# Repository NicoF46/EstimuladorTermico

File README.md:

# EstimuladorTermico
Estimulador térmico para trabajo profesional

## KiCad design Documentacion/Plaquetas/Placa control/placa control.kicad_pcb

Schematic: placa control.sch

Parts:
A1: Arduino_Nano_v3.x; Arduino_Nano
C1: 2u; C_Disc_D4.7mm_W2.5mm_P5.00mm
C2, C9: 100n; C_Disc_D4.7mm_W2.5mm_P5.00mm
C3: 330n; C_Disc_D4.7mm_W2.5mm_P5.00mm
C4, C6: 2.2n; C_Disc_D4.7mm_W2.5mm_P5.00mm
C7: 4700u; C_Radial_D16.0mm_H25.0mm_P7.50mm
C8: 4.7u; C_Rect_L29.0mm_W9.1mm_P27.50mm_MKT
C10, C11: 4.7n; C_Disc_D4.7mm_W2.5mm_P5.00mm
D1: 1N4002; D_DO-41_SOD81_P10.16mm_Horizontal
D6: Yellow; D_A-405_P7.62mm_Horizontal
D7: Green; D_A-405_P7.62mm_Horizontal
D8: RED; D_A-405_P7.62mm_Horizontal
J1, J5, J8: Conn_01x02_Male; PinHeader_1x02_P2.54mm_Vertical
J2: DB9_Female_MountingHoles; DSUB-9_Female_Horizontal_P2.77x2.84mm_EdgePinOffset7.70mm_H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
J3: Screw_Terminal_01x02; TerminalBlock_bornier-2_P5.08mm
J4: Conn_01x06_Male; PinHeader_1x06_P2.54mm_Vertical
J6: Conn_01x04_Male; PinHeader_1x04_P2.54mm_Vertical
J7: Conn_02x05_Counter_Clockwise; PinHeader_2x05_P2.54mm_VerticalNico
J9: Conn_01x08_Male; PinHeader_1x08_P2.54mm_Vertical
J10: Conn_01x06_Female; PinHeader_1x06_P2.54mm_Vertical
J11, J12, J13: Conn_01x03_Male; PinHeader_1x03_P2.54mm_Vertical
Q1, Q2, Q7, Q8, Q9: BC548; TO-92_HandSolder
R1, R2, R18, R19, R20: 220; R_Axial_DIN0414_L11.9mm_D4.5mm_P15.24mm_Horizontal
R3, R4, R5, R6, R7, R8: 10k; R_Axial_DIN0414_L11.9mm_D4.5mm_P15.24mm_Horizontal
U1: LM7805_TO220; TO-220-3_Vertical

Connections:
BUZZER: A1.14, R1.2
GND: A1.4, A1.29, C1.2, C2.2, C3.2, C4.2, C6.2, C7.2, C8.2, C9.2, C10.2, C11.2, J3.2, J5.1, J6.4, J7.7, J7.8, R2.2, R3.2, R8.2, R18.2, R19.2, R20.2, U1.2 (GND)
GND_C: J2.0 (PAD), J2.7, J2.8, J12.1, J12.2, J12.3
unnamed: A1.18, C9.1
unnamed: C1.1, Q1.2 (B), R1.1
unnamed: C3.1, D1.1 (K), U1.1 (VI)
unnamed: D6.1 (K), J10.3
unnamed: D6.2 (A), J10.4
unnamed: D7.1 (K), J10.5
unnamed: D7.2 (A), J10.6
unnamed: D8.1 (K), J10.1
unnamed: D8.2 (A), J10.2
unnamed: J5.2, Q1.3 (E)
unnamed: J9.1, Q8.1 (C)
unnamed: J9.3, Q9.1 (C)
unnamed: J9.5, Q2.1 (C)
unnamed: J9.7, Q7.1 (C)
unnamed: Q2.3 (E), R2.1
unnamed: Q7.3 (E), R18.1
unnamed: Q8.3 (E), R19.1
unnamed: Q9.3 (E), R20.1
PIN-COLD-LED-BLUE: A1.11, Q2.2 (B)
PIN-HOT-LED-YELLOW: A1.10, Q7.2 (B)
PIN-READY-LED-GREEN: A1.22, Q8.2 (B)
PIN-WARNING-LED-RED: A1.21, Q9.2 (B)
PIN_SENSOR_TEMPERATURA_1: A1.25, C11.1, J7.2, R8.1
PIN_SENSOR_TEMPERATURA_2: A1.26, C10.1, J7.1, R3.1
PMOS_CALOR: A1.9, J4.1
PMOS_FRIO: A1.8, J4.5
PWM_CALOR: A1.12, J4.3
PWM_FRIO: A1.13, J4.6
REF_5: A1.27, C2.1, J6.1, J7.10, Q1.1 (C), R4.1, R5.1, R6.1, R7.1, U1.3 (VO)
REF_5C: J2.5, J11.1
SCL-DISPLAY: A1.24, J6.3, R7.2
SDA-DISPLAY: A1.23, J6.2, R6.2
SENSOR_FAN: A1.20, C4.1, J7.3, R5.2
SENSOR_PUMP: A1.19, C6.1, J7.4, R4.2
VCC: C7.1, C8.1, D1.2 (A), J3.1, J7.5, J7.6, J9.2, J9.4, J9.6, J9.8
VCC_C: J2.3, J2.6, J13.1, J13.2, J13.3
fan_sensor_C: J1.1, J2.1
pump_sensor_C: J1.2, J2.9
term_1C: J2.2, J11.3
term_2C: J2.4, J11.2

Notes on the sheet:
Microcontrolador
Sensor de temperatura del peltier
Conector a placa del gabinete del peltier
Conector a placa de potencia
Conector a leds
Sensores Water Cooling
Alimentación 12 V
Referencia de 5 V
Placa de conexion: chasis - placa de control
Conector hacia peltier
LEDS
Conector hacia placa control
BUZZER
Pull up resistors
Conector display
5 V

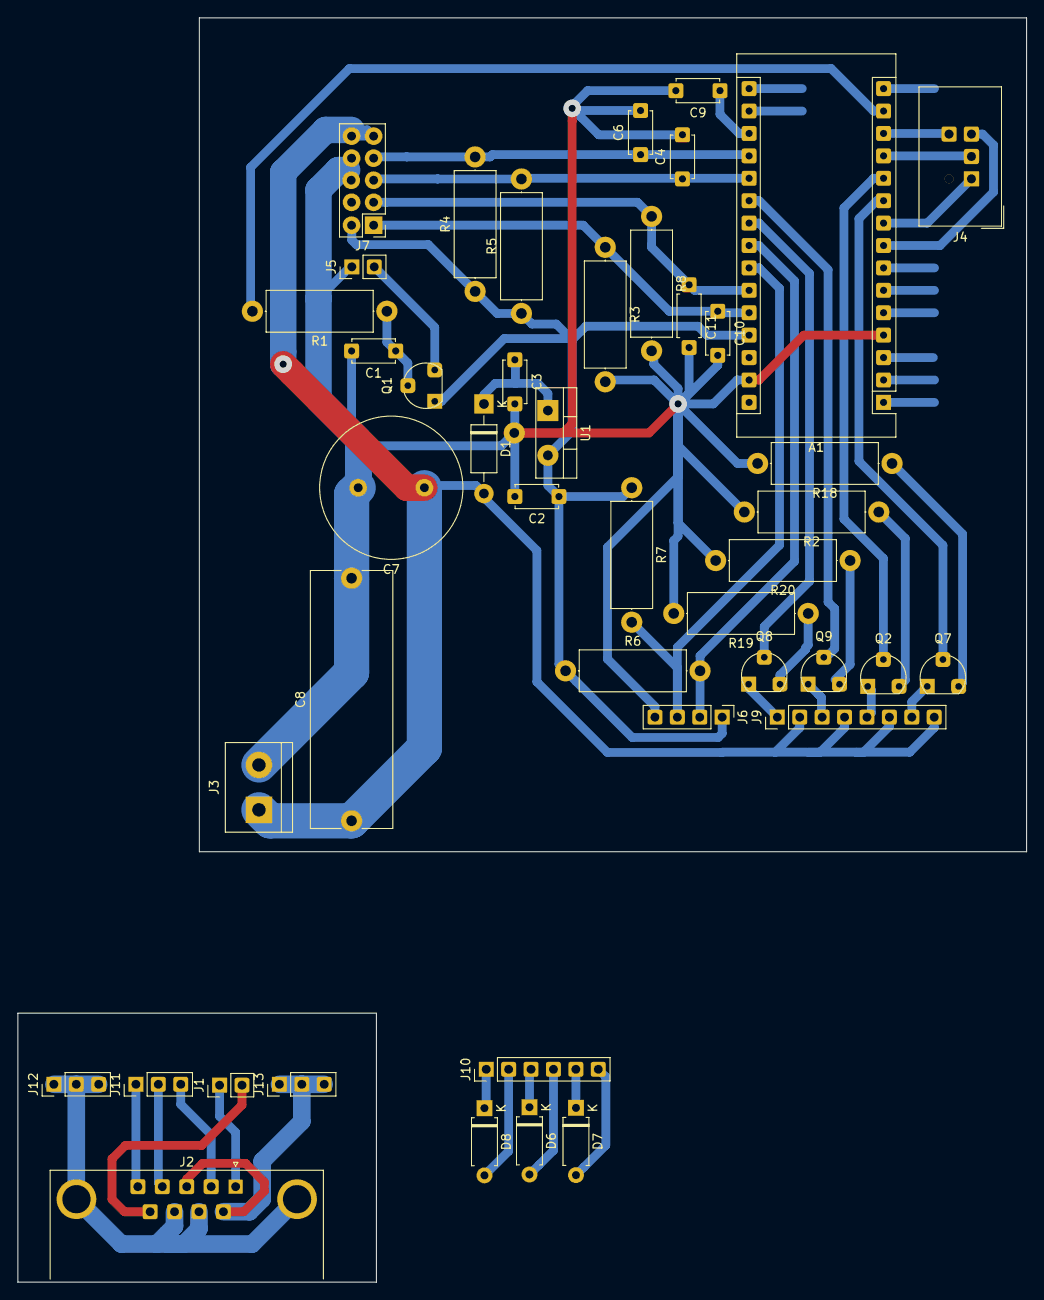
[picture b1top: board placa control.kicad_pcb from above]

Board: 2 copper layers, 114.3 x 143.3 mm, 44 parts (0 on the bottom side), 43 nets.

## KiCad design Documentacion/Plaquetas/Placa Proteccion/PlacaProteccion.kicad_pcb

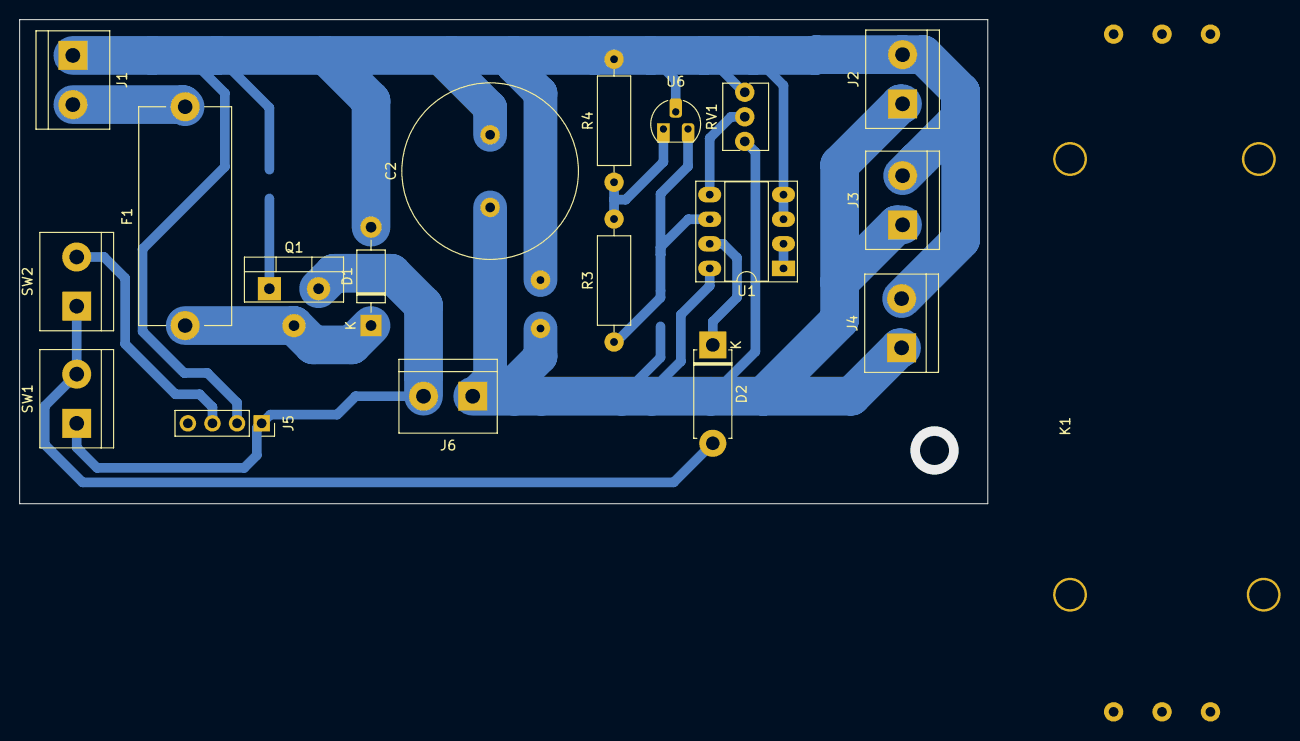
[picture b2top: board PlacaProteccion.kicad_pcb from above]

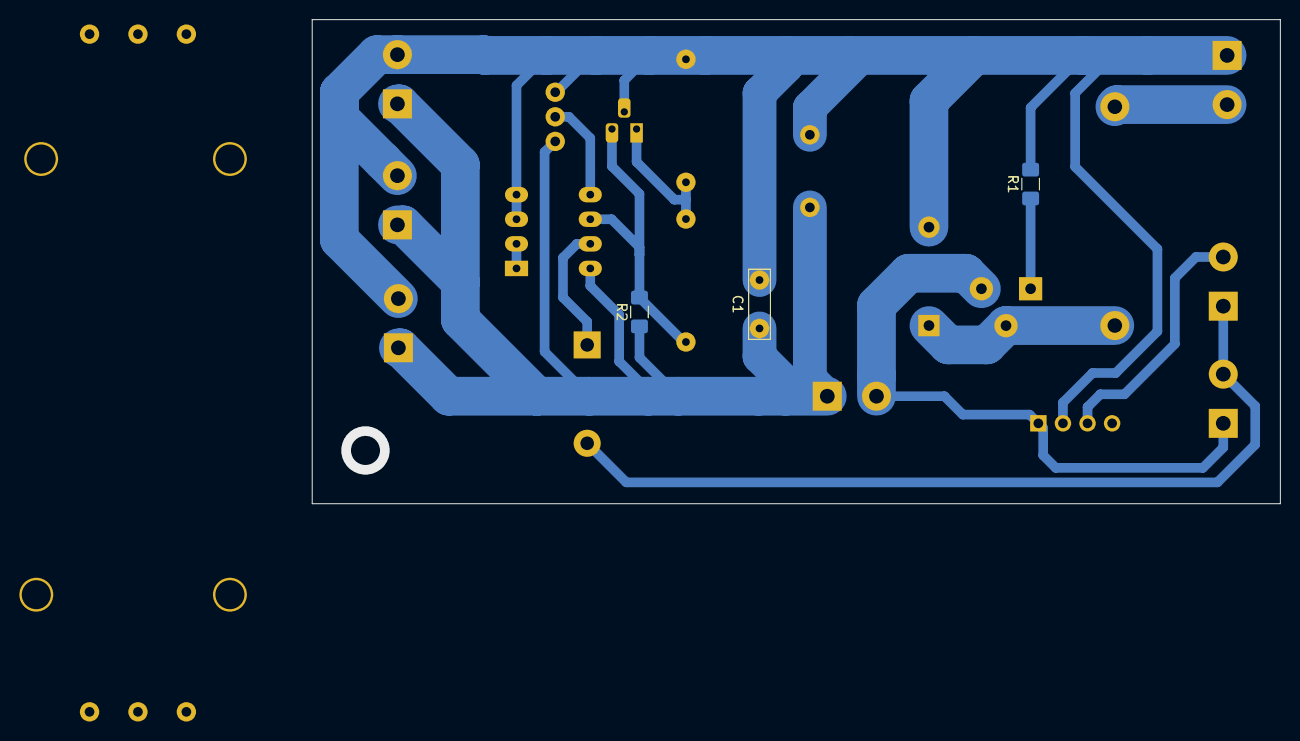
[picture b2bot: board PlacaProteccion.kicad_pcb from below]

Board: 2 copper layers, 100.0 x 50.0 mm, 22 parts (3 on the bottom side), 13 nets.

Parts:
C1: 1u; C_Rect_L7.0mm_W2.0mm_P5.00mm
C2: 1000u; C_Radial_D18.0mm_H35.5mm_P7.50mm
D1: 1N4007; D_DO-41_SOD81_P10.16mm_Horizontal
D2: DIODE; D_5W_P10.16mm_Horizontal
F1: Fuse; Fuseholder_Cylinder-5x20mm_Stelvio-Kontek_PTF78_Horizontal_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
J1: POW_IN; TerminalBlock_bornier-2_P5.08mm
J2, J3, J4: POW_OUT; TerminalBlock_bornier-2_P5.08mm
J5: RELAY_CTRL; PinSocket_1x04_P2.54mm_Vertical
J6: RELAY_SW; TerminalBlock_bornier-2_P5.08mm
K1: Modulo_Relé; Modulo_Relé_Arduino
Q1: IRF4905; TO-220-3_Vertical
R1: 100k; R_1206_3216Metric_Pad1.42x1.75mm_HandSolder
R2: 1.5k; R_1206_3216Metric_Pad1.42x1.75mm_HandSolder
R3, R4: 100k; R_Axial_DIN0309_L9.0mm_D3.2mm_P12.70mm_Horizontal
RV1: R_POT; Potentiometer_Bourns_3266Y_Vertical
SW1: ON_SW; TerminalBlock_bornier-2_P5.08mm
SW2: OFF_SW; TerminalBlock_bornier-2_P5.08mm
U1: LM2903; DIP-8_W7.62mm_Socket_LongPads
U6: TL431LP; TO-92_HandSolder

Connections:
unnamed: D1.1, F1.1, Q1.2
unnamed: D2.1, U1.7
unnamed: D2.2, SW1.2, SW2.1
unnamed: J5.3, SW2.2
unnamed: Q1.1, R1.1
unnamed: R2.2, R3.1, U1.6, U6.3
unnamed: R3.2, R4.1, U6.1
unnamed: RV1.2, U1.5
unnamed: U1.1, U1.2
POW_IN+: F1.2, J1.2
POW_IN-: C1.2, C2.2, D1.2, J1.1, J2.2, J3.2, J4.2, J5.2, R1.2, R4.2, RV1.1, U1.3, U1.4, U6.2
RELAY_COM: J5.1, J6.2, Q1.3, SW1.1
RELAY_NO: C1.1, C2.1, J2.1, J3.1, J4.1, J6.1, R2.1, RV1.3, U1.8

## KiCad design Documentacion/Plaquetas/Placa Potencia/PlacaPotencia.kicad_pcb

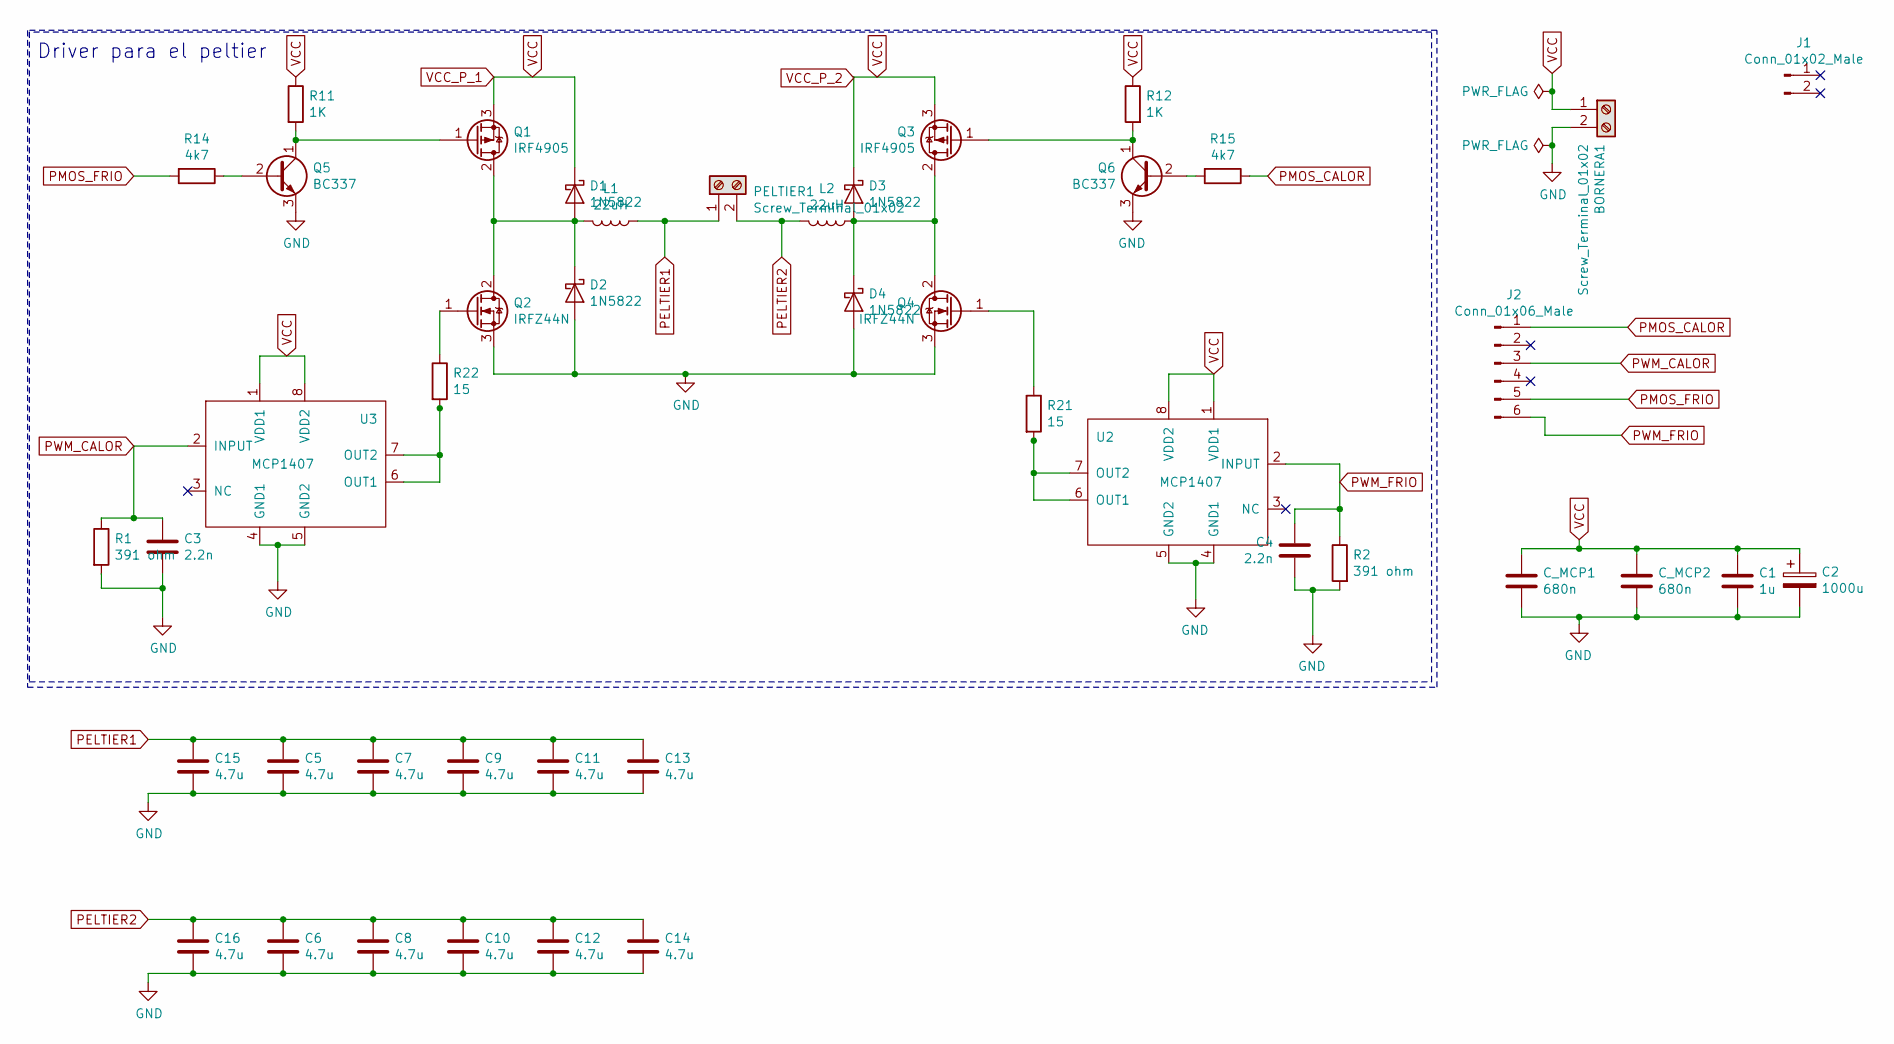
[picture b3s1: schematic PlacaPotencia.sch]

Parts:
BORNERA1: Screw_Terminal_01x02; TerminalBlock_bornier-2_P5.08mm
C1: 1u; C_Rect_L16.5mm_W10.7mm_P15.00mm_MKT
C2: 1000u; CP_Radial_D10.0mm_P5.00mm
C3, C4: 2.2n; C_1206_3216Metric_Pad1.42x1.75mm_HandSolder
C5, C6, C7, C8, C9, C10, C11, C12, C13, C14, C15, C16: 4.7u; C_Rect_L29.0mm_W9.1mm_P27.50mm_MKT
C_MCP1, C_MCP2: 680n; C_Rect_L21.5mm_W5.5mm_P20.00mm_MKS4
D1, D2, D3, D4: 1N5822; D_DO-201AD_P15.24mm_Horizontal
J1: Conn_01x02_Male; disipadorFETS
J2: Conn_01x06_Male; IDC-Header_2x03_P2.54mm_Vertical
L1, L2: 22uH; L_Radial_D10.0mm_P5.00mm_Neosid_SD12k_style3
PELTIER1: Screw_Terminal_01x02; TerminalBlock_bornier-2_P5.08mm
Q1, Q3: IRF4905; TO-220-3_Vertical
Q2, Q4: IRFZ44N; TO-220-3_Vertical
Q5, Q6: BC337; TO-92_HandSolder
R1, R2: 391 ohm; R_1206_3216Metric
R11, R12: 1K; R_1206_3216Metric
R14, R15: 4k7; R_1206_3216Metric
R21, R22: 15; R_Axial_DIN0411_L9.9mm_D3.6mm_P12.70mm_Horizontal
U2, U3: MCP1407; SOIC-8-1EP_3.9x4.9mm_P1.27mm_EP2.41x3.3mm

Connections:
GND: BORNERA1.2, C1.2, C2.2, C3.2, C4.2, C5.2, C6.2, C7.2, C8.2, C9.2, C10.2, C11.2, C12.2, C13.2, C14.2, C15.2, C16.2, C_MCP1.2, C_MCP2.2, D2.2 (A), D4.2 (A), Q2.3 (S), Q4.3 (S), Q5.3 (E), Q6.3 (E), R1.2, R2.2, U2.4 (GND1), U2.5 (GND2), U3.4 (GND1), U3.5 (GND2)
unnamed: D1.2 (A), D2.1 (K), L1.2, Q1.2 (D), Q2.2 (D)
unnamed: D3.2 (A), D4.1 (K), L2.1, Q3.2 (D), Q4.2 (D)
unnamed: Q1.1 (G), Q5.1 (C), R11.2
unnamed: Q2.1 (G), R22.1
unnamed: Q3.1 (G), Q6.1 (C), R12.2
unnamed: Q4.1 (G), R21.1
unnamed: Q5.2 (B), R14.1
unnamed: Q6.2 (B), R15.2
unnamed: R21.2, U2.6 (OUT1), U2.7 (OUT2)
unnamed: R22.2, U3.6 (OUT1), U3.7 (OUT2)
PELTIER1: C5.1, C7.1, C9.1, C11.1, C13.1, C15.1, L1.1, PELTIER1.1
PELTIER2: C6.1, C8.1, C10.1, C12.1, C14.1, C16.1, L2.2, PELTIER1.2
PMOS_CALOR: J2.1, R15.1
PMOS_FRIO: J2.5, R14.2
PWM_CALOR: C3.1, J2.3, R1.1, U3.2 (INPUT)
PWM_FRIO: C4.1, J2.6, R2.1, U2.2 (INPUT)
VCC: BORNERA1.1, C1.1, C2.1, C_MCP1.1, C_MCP2.1, D1.1 (K), D3.1 (K), Q1.3 (S), Q3.3 (S), R11.1, R12.1, U2.1 (VDD1), U2.8 (VDD2), U3.1 (VDD1), U3.8 (VDD2)

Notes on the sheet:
Driver para el peltier

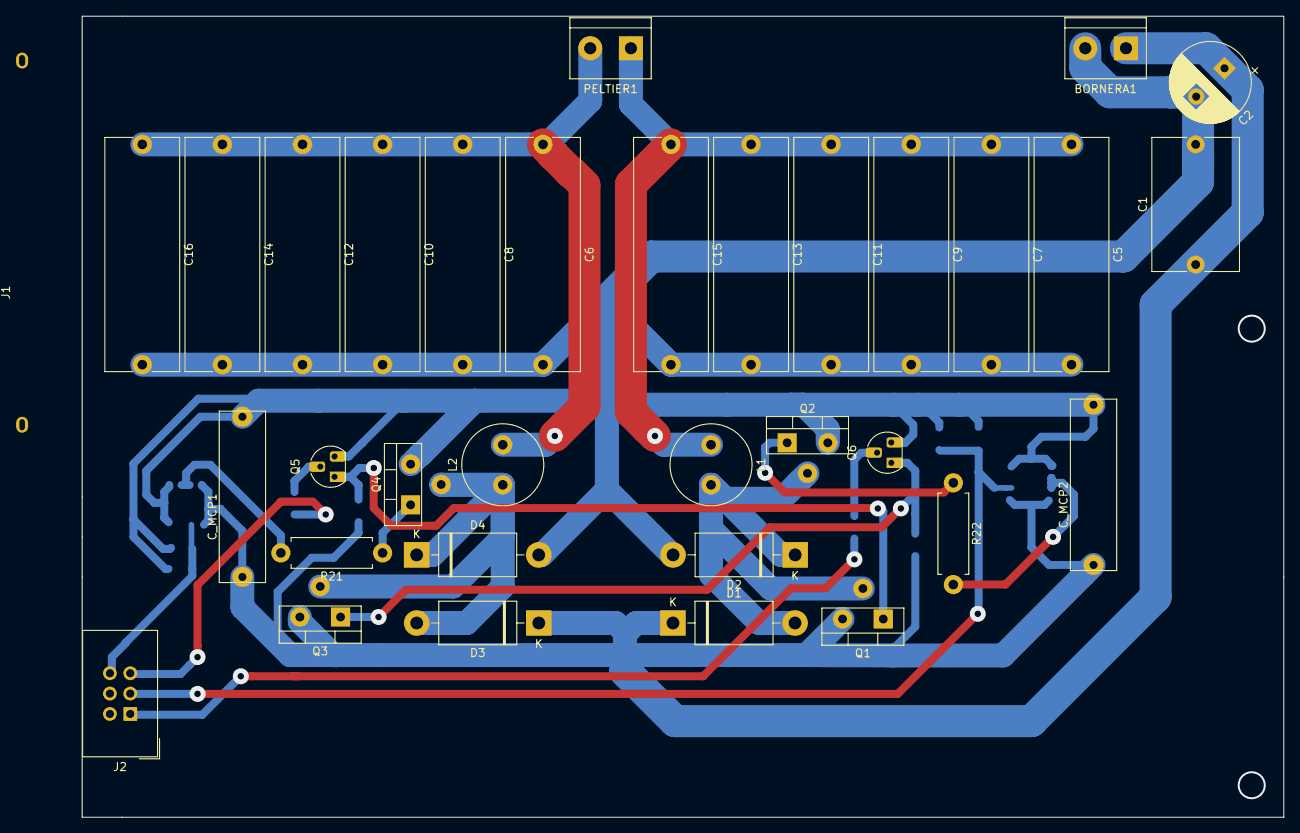
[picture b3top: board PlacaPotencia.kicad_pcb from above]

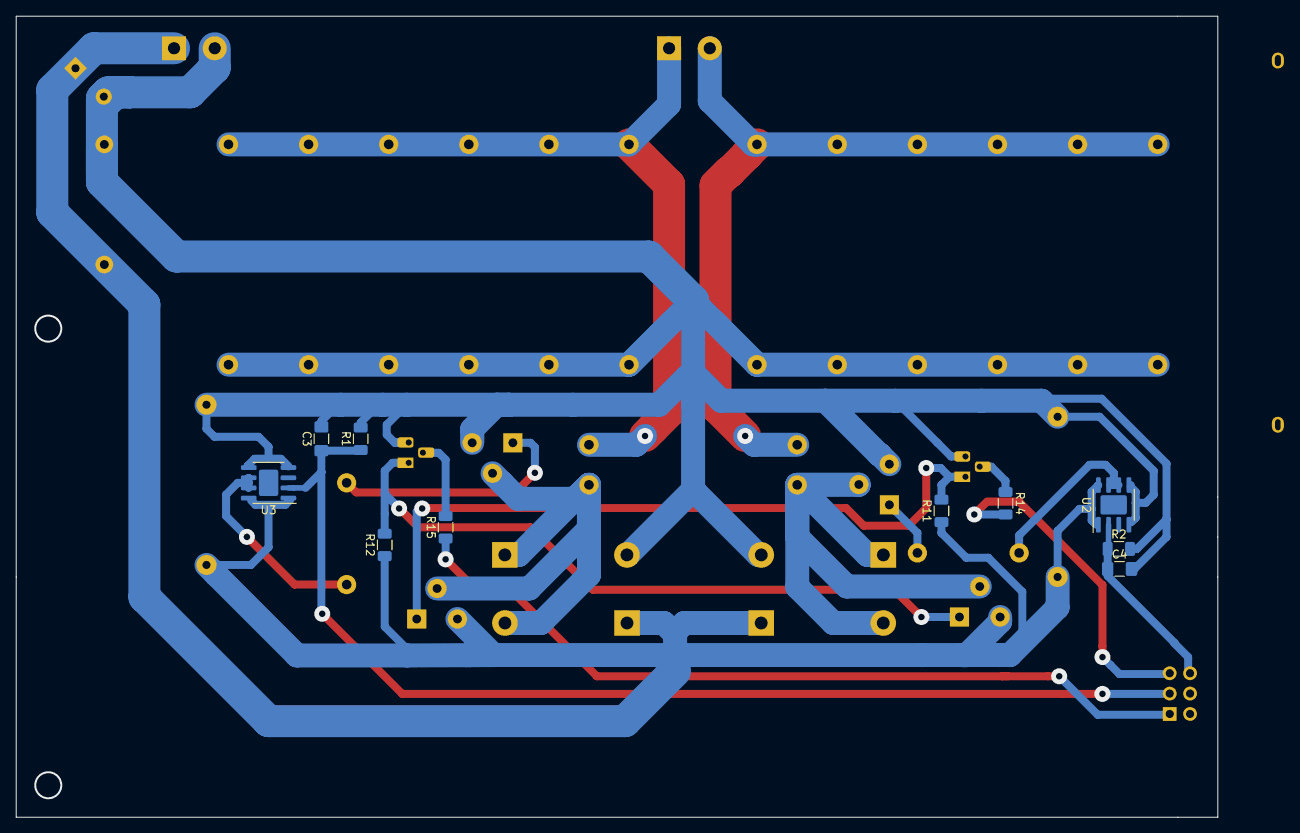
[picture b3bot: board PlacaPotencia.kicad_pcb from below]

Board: 2 copper layers, 150.0 x 100.0 mm, 44 parts (10 on the bottom side), 18 nets.

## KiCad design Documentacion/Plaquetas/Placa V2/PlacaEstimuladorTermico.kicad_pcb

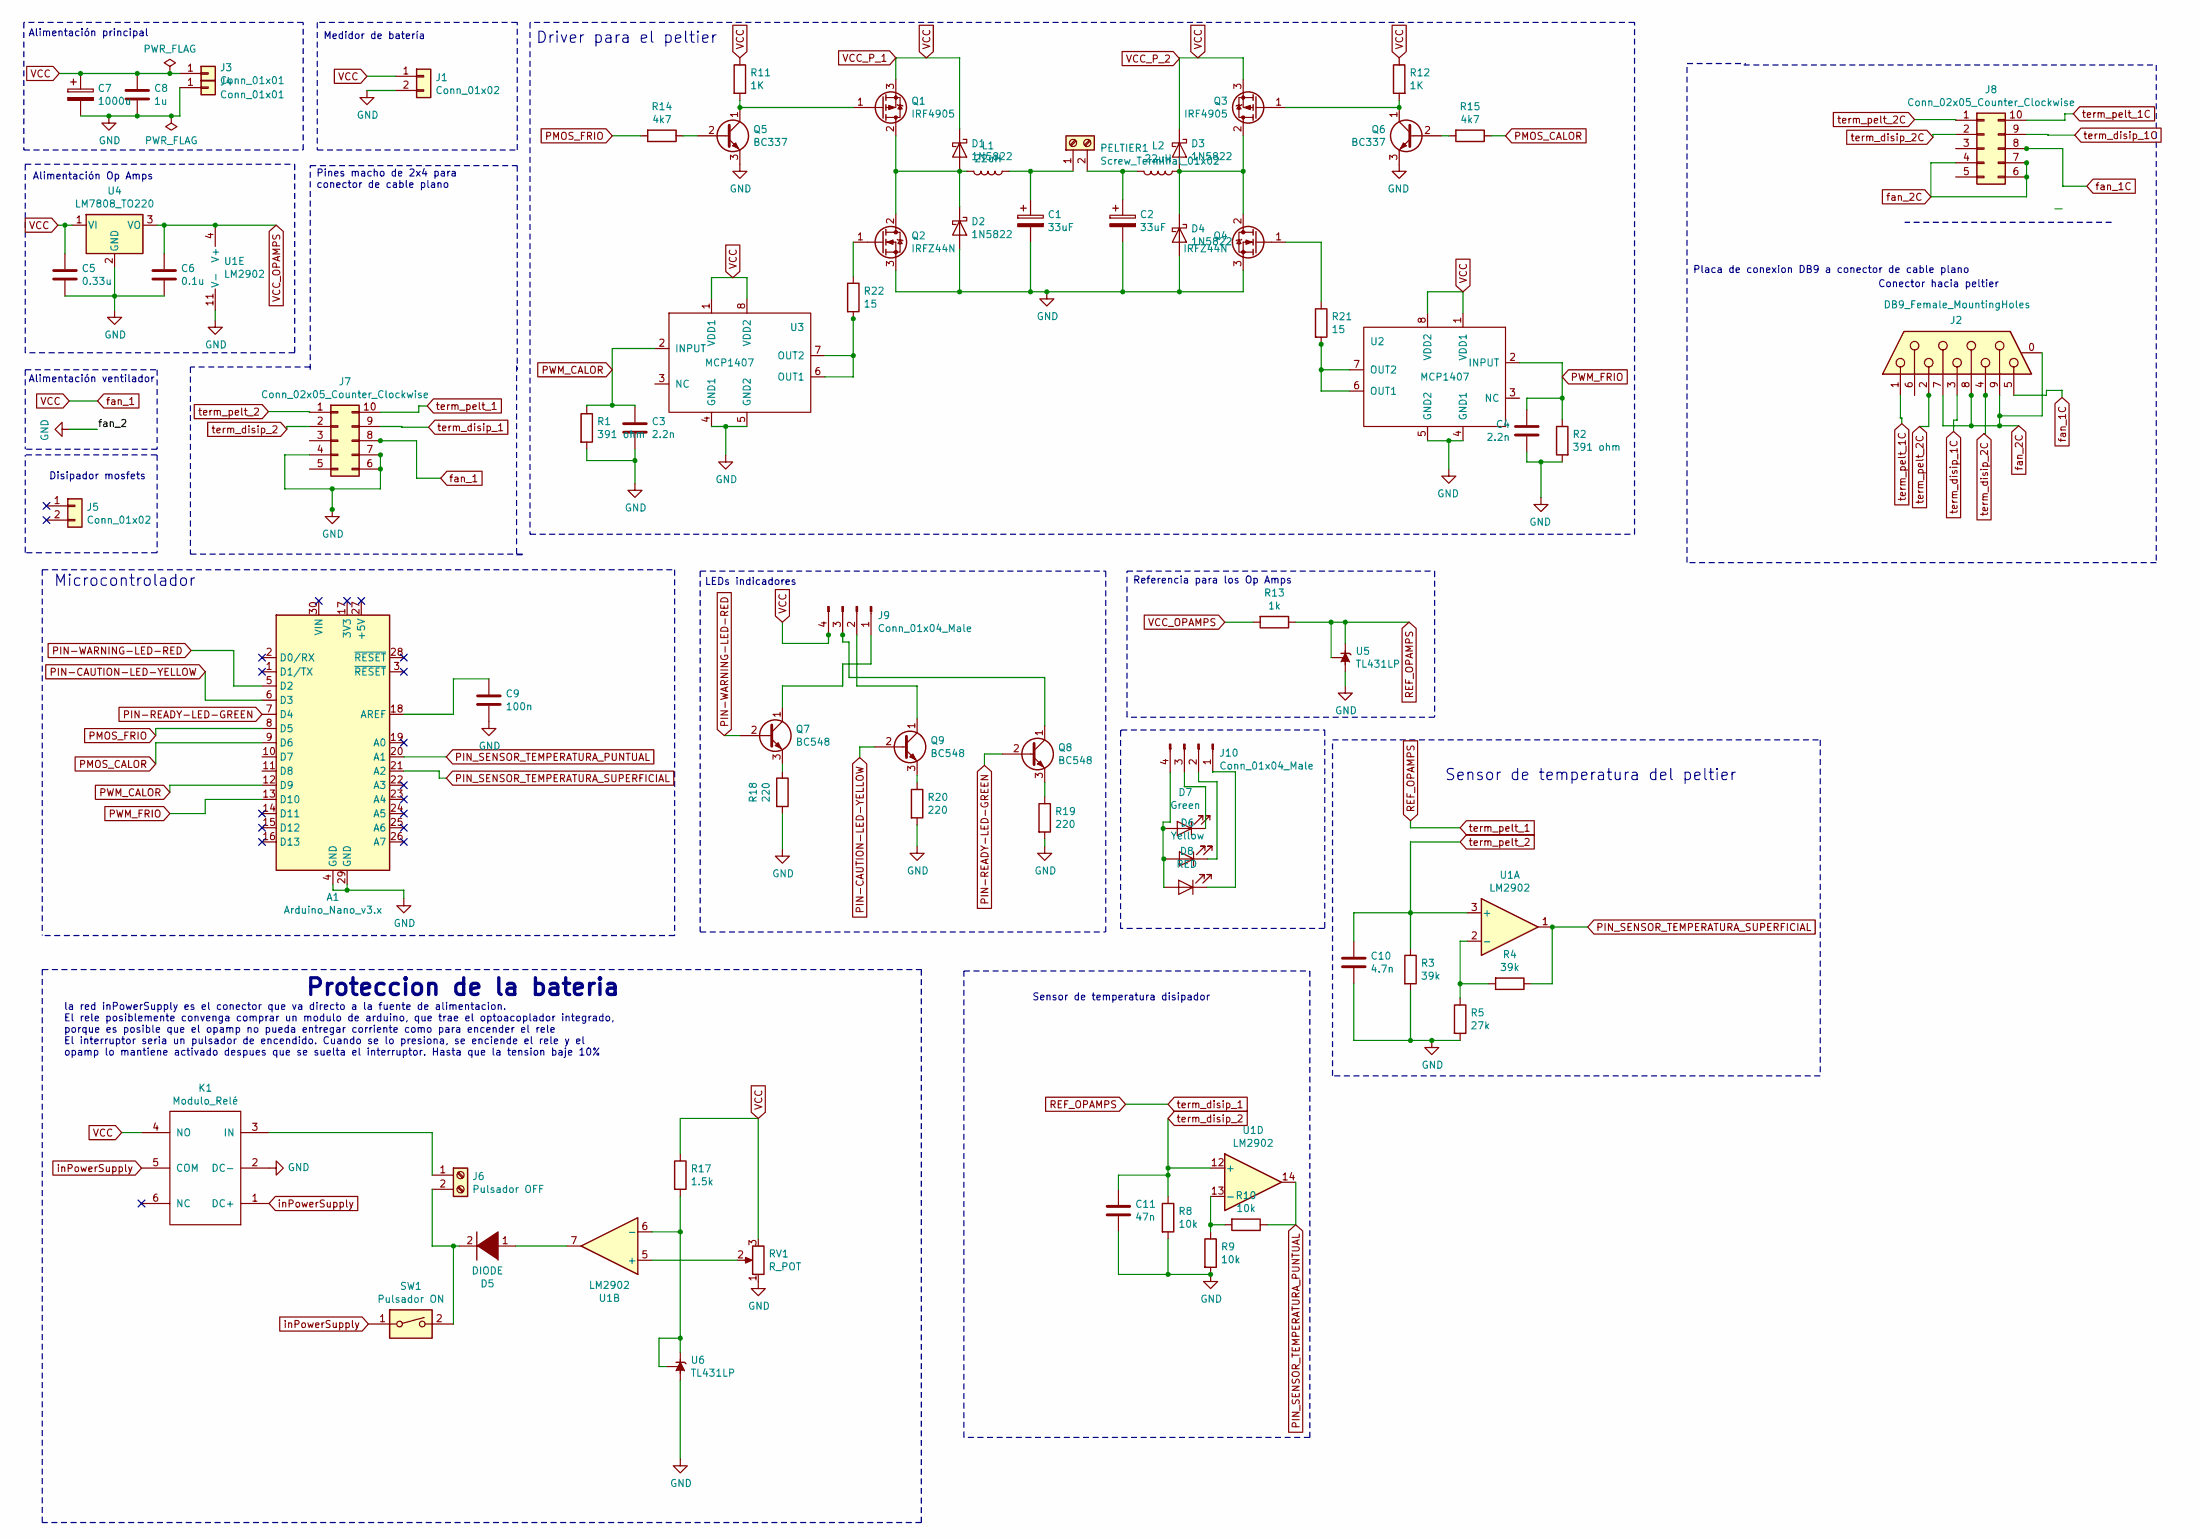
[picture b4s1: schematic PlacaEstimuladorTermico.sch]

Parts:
A1: Arduino_Nano_v3.x; Arduino_Nano
C1, C2: 33uF; CP_Radial_D13.0mm_P7.50mm
C3, C4: 2.2n; C_1206_3216Metric_Pad1.42x1.75mm_HandSolder
C5: 0.33u; C_1206_3216Metric_Pad1.42x1.75mm_HandSolder
C6: 0.1u; C_1206_3216Metric_Pad1.42x1.75mm_HandSolder
C7: 1000u; C_Radial_D18.0mm_H35.5mm_P7.50mm
C8: 1u; C_1206_3216Metric_Pad1.42x1.75mm_HandSolder
C9: 100n; C_1206_3216Metric_Pad1.42x1.75mm_HandSolder
C10: 4.7n; C_1206_3216Metric_Pad1.42x1.75mm_HandSolder
C11: 47n; C_1206_3216Metric_Pad1.42x1.75mm_HandSolder
D1, D2, D3, D4: 1N5822; D_DO-201AD_P15.24mm_Horizontal
D5: DIODE; D_5W_P10.16mm_Horizontal
D6: Yellow; D_A-405_P7.62mm_Horizontal
D7: Green; D_A-405_P7.62mm_Horizontal
D8: RED; D_A-405_P7.62mm_Horizontal
J1: Conn_01x02; PinSocket_1x02_P2.54mm_Vertical
J2: DB9_Female_MountingHoles; DSUB-9_Female_Horizontal_P2.77x2.84mm_EdgePinOffset7.70mm_H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
J3, J4: Conn_01x01; Banana_Jack_1Pin
J5: Conn_01x02; disipadorFETS
J6: Pulsador OFF; TerminalBlock_bornier-2_P5.08mm
J7: Conn_02x05_Counter_Clockwise; PinHeader_2x05_P2.54mm_VerticalNico
J8: Conn_02x05_Counter_Clockwise; PinHeader_2x05_P2.54mm_Vertical
J9, J10: Conn_01x04_Male; PinHeader_1x04_P2.54mm_Vertical
K1: Modulo_Relé; Modulo_Relé_Arduino
L1, L2: 22uH; L_Radial_D10.0mm_P5.00mm_Neosid_SD12k_style3
PELTIER1: Screw_Terminal_01x02; TerminalBlock_bornier-2_P5.08mm
Q1, Q3: IRF4905; TO-220-3_Vertical
Q2, Q4: IRFZ44N; TO-220-3_Vertical
Q5, Q6: BC337; TO-92_HandSolder
Q7, Q8, Q9: BC548; TO-92_HandSolder
R1, R2: 391 ohm; R_1206_3216Metric
R3, R4: 39k; R_1206_3216Metric
R5: 27k; R_1206_3216Metric
R8, R9, R10: 10k; R_1206_3216Metric
R11, R12: 1K; R_1206_3216Metric
R13: 1k; R_1206_3216Metric
R14, R15: 4k7; R_1206_3216Metric
R17: 1.5k; R_1206_3216Metric
R18, R19, R20: 220; R_1206_3216Metric
R21, R22: 15; R_Axial_DIN0204_L3.6mm_D1.6mm_P5.08mm_Horizontal
RV1: R_POT; Potentiometer_Bourns_3266Y_Vertical
SW1: Pulsador ON; TerminalBlock_bornier-2_P5.08mm
U1: LM2902; DIP-14_W8.89mm_SMDSocket_LongPads
U2, U3: MCP1407; SOIC-8-1EP_3.9x4.9mm_P1.27mm_EP2.41x3.3mm
U4: LM7808_TO220; TO-220-3_Vertical
U5: TL431LP; TO-92_HandSolder
U6: TL431LP; TO-92_Inline

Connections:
GND: A1.4 (GND), A1.29 (GND), C1.2, C2.2, C3.2, C4.2, C5.2, C6.2, C7.2, C8.2, C9.2, C10.2, C11.2, D2.2 (A), D4.2 (A), J1.2, J4.1, J7.4, J7.6, J7.7, K1.2 (DC-), Q2.3 (S), Q4.3 (S), Q5.3 (E), Q6.3 (E), R1.2, R2.2, R3.2, R5.2, R8.2, R9.2, R18.2, R19.2, R20.2, RV1.1, U1.11 (V-), U2.4 (GND1), U2.5 (GND2), U3.4 (GND1), U3.5 (GND2), U4.2 (GND), U5.2 (A), U6.2 (A); also elsewhere on the board
unnamed: A1.18 (AREF), C9.1
unnamed 17: A1.27 (+5V); also elsewhere on the board
unnamed: C1.1, L1.1, PELTIER1.1
unnamed: C2.1, L2.2, PELTIER1.2
unnamed: D1.2 (A), D2.1 (K), L1.2, Q1.2 (D), Q2.2 (D)
unnamed: D3.2 (A), D4.1 (K), L2.1, Q3.2 (D), Q4.2 (D)
unnamed: D5.1 (K), U1.7
unnamed: D5.2 (A), J6.2, SW1.2
unnamed: D6.1 (K), J10.2
unnamed: D6.2 (A), D7.2 (A), D8.2 (A), J10.4
unnamed: D7.1 (K), J10.3
unnamed: D8.1 (K), J10.1
unnamed: J6.1, K1.3 (IN)
unnamed: J9.1, Q7.1 (C)
unnamed: J9.2, Q9.1 (C)
unnamed: J9.3, Q8.1 (C)
unnamed: Q1.1 (G), Q5.1 (C), R11.2
unnamed: Q2.1 (G), R22.1
unnamed: Q3.1 (G), Q6.1 (C), R12.2
unnamed: Q4.1 (G), R21.1
unnamed: Q5.2 (B), R14.1
unnamed: Q6.2 (B), R15.2
unnamed: Q7.3 (E), R18.1
unnamed: Q8.3 (E), R19.1
unnamed: Q9.3 (E), R20.1
unnamed: R4.2, R5.1, U1.2 (-)
unnamed: R9.1, R10.2, U1.13 (-)
unnamed: R17.2, U1.6 (-), U6.1 (REF), U6.3 (K)
unnamed: R21.2, U2.6 (OUT1), U2.7 (OUT2)
unnamed: R22.2, U3.6 (OUT1), U3.7 (OUT2)
unnamed: RV1.2, U1.5 (+)
PIN-CAUTION-LED-YELLOW: A1.6 (D3), Q9.2 (B)
PIN-READY-LED-GREEN: A1.7 (D4), Q8.2 (B)
PIN-WARNING-LED-RED: A1.5 (D2), Q7.2 (B)
PIN_SENSOR_TEMPERATURA_PUNTUAL: A1.20 (A1), R10.1, U1.14
PIN_SENSOR_TEMPERATURA_SUPERFICIAL: A1.21 (A2), R4.1, U1.1
PMOS_CALOR: A1.9 (D6), R15.1
PMOS_FRIO: A1.8 (D5), R14.2
PWM_CALOR: A1.12 (D9), C3.1, R1.1, U3.2 (INPUT)
PWM_FRIO: A1.13 (D10), C4.1, R2.1, U2.2 (INPUT)
REF_OPAMPS: J7.9, J7.10, R13.1, U5.1 (REF), U5.3 (K)
VCC_OPAMPS: C6.1, R13.2, U1.4 (V+), U4.3 (VO)
fan_1C: J2.5, J8.8
fan_2C: J2.0 (PAD), J2.7, J2.8, J2.9, J8.4, J8.6, J8.7
inPowerSupply: K1.1 (DC+), K1.5 (COM), SW1.1
term_disip_1C: J2.3, J8.9
term_disip_2: C11.1, J7.2, R8.1, U1.12 (+)
term_disip_2C: J2.4, J8.2
term_pelt_1C: J2.1, J8.10
term_pelt_2: C10.1, J7.1, R3.1, U1.3 (+)
term_pelt_2C: J2.2, J8.1

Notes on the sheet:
la red inPowerSupply es el conector que va directo a la fuente de alimentacion. El rele posiblemente convenga comprar un modulo de arduino, que trae el optoacoplador integrado, porque es posible que el opamp no pueda entregar corriente como para encender el rele El interruptor seria un pulsador de 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
Proteccion de la bateria
Alimentación principal
Medidor de batería
Referencia para los Op Amps
Alimentación Op Amps
Driver para el peltier
Microcontrolador
LEDs indicadores
Sensor de temperatura disipador
Sensor de temperatura del peltier
Alimentación ventilador
Disipador mosfets
Conector hacia peltier
Placa de conexion DB9 a conector de cable plano
Pines macho de 2x4 para conector de cable plano

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
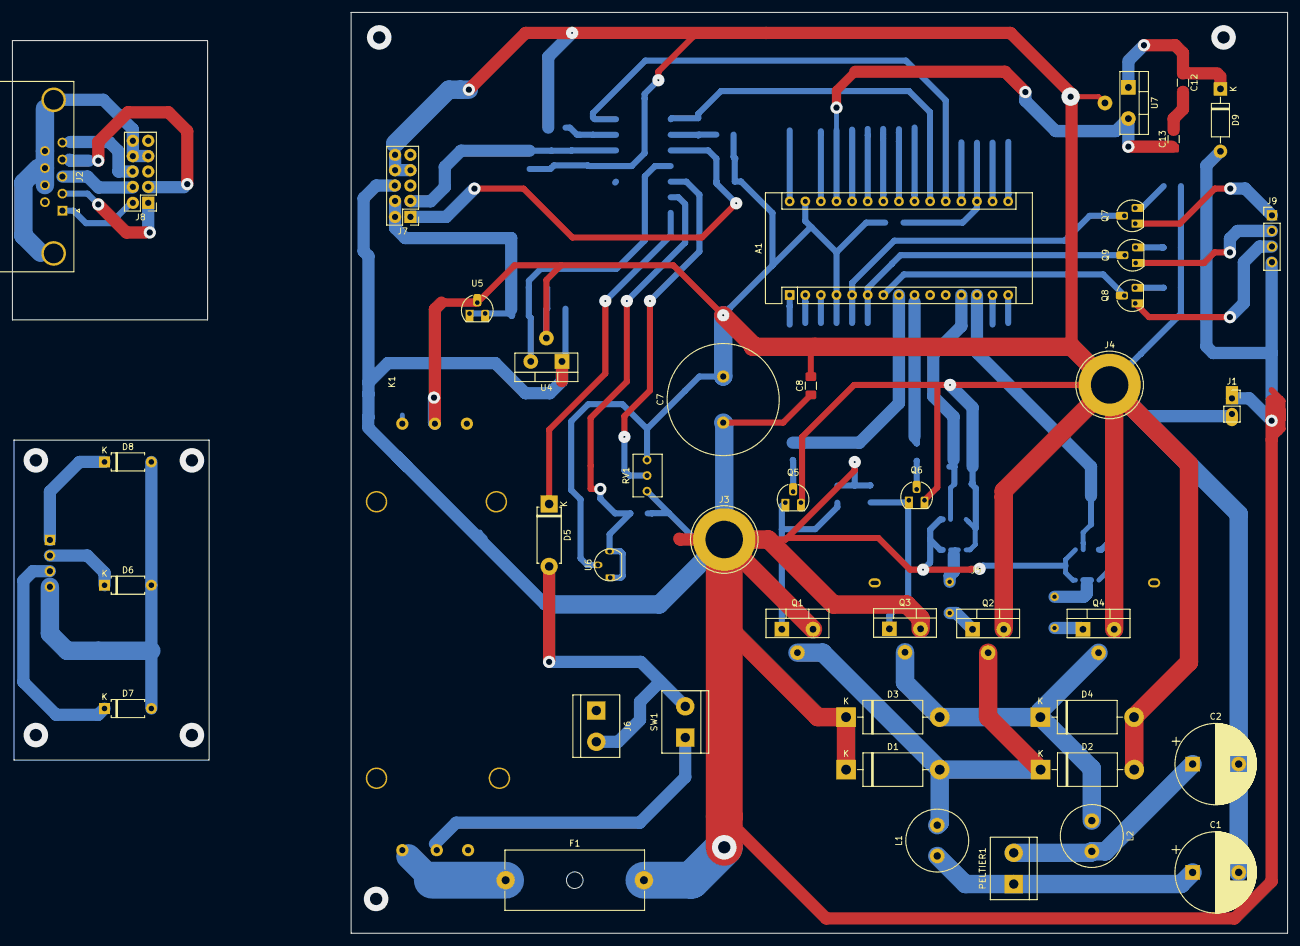
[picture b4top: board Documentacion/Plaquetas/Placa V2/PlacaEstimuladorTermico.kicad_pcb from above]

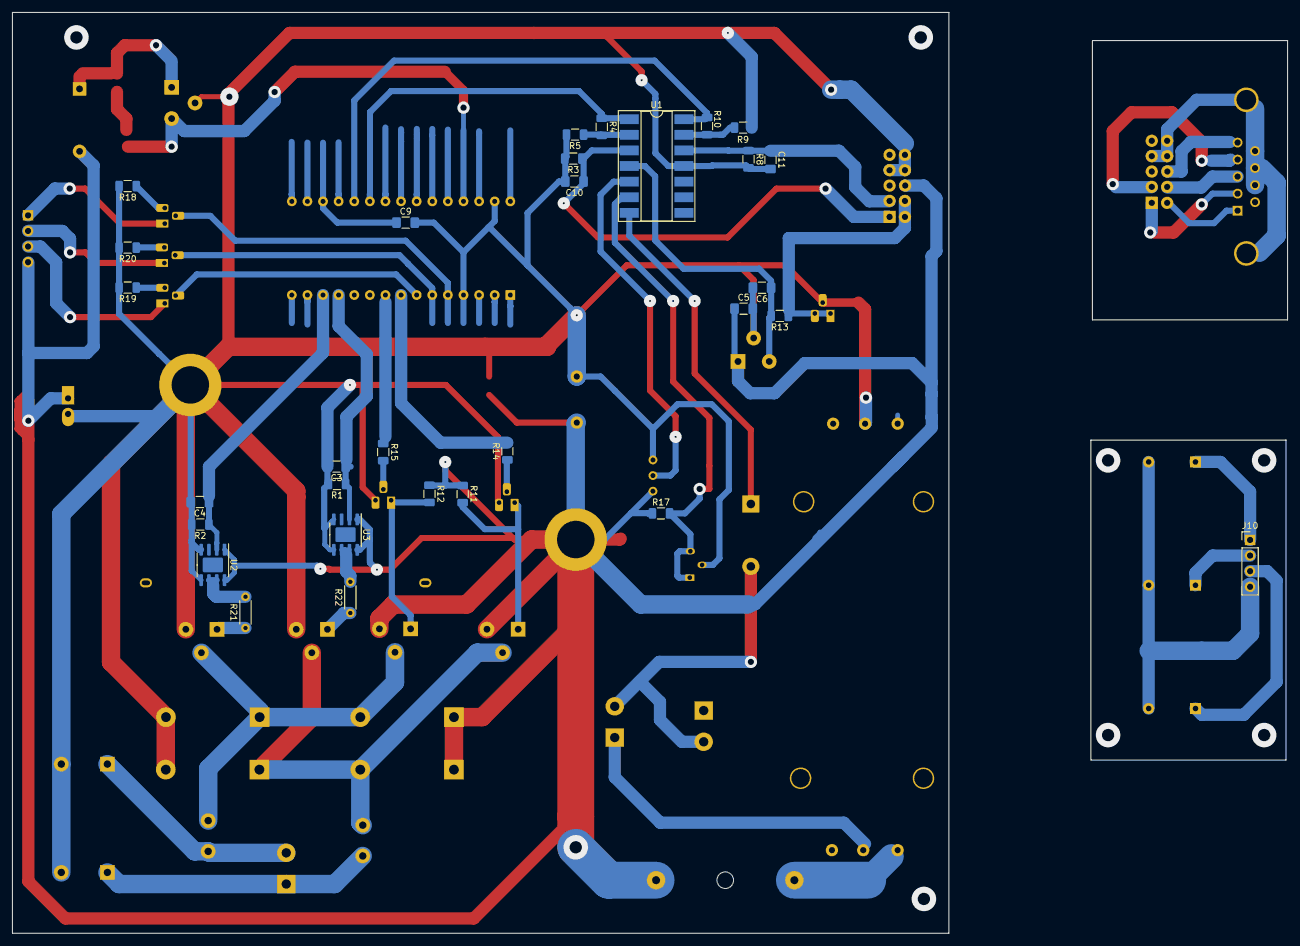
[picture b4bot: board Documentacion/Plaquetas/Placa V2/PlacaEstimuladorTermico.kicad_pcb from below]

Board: 2 copper layers, 152.4 x 149.9 mm, 75 parts (30 on the bottom side), 56 nets.

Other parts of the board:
C12: 0.33u; C_1206_3216Metric_Pad1.42x1.75mm_HandSolder
C13: 0.1u; C_1206_3216Metric_Pad1.42x1.75mm_HandSolder
D9: 1N4002; D_DO-41_SOD81_P10.16mm_Horizontal
F1: Fuse; Fuseholder_Cylinder-5x20mm_Schurter_0031_8201_Horizontal_Op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
U7: L7805; TO-220-3_Vertical

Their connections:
GND: U7.2; also elsewhere on the board
unnamed 17: C13.1, U7.3; also elsewhere on the board
unnamed: C12.1, D9.1, U7.1
unnamed: C12.2, C13.2
